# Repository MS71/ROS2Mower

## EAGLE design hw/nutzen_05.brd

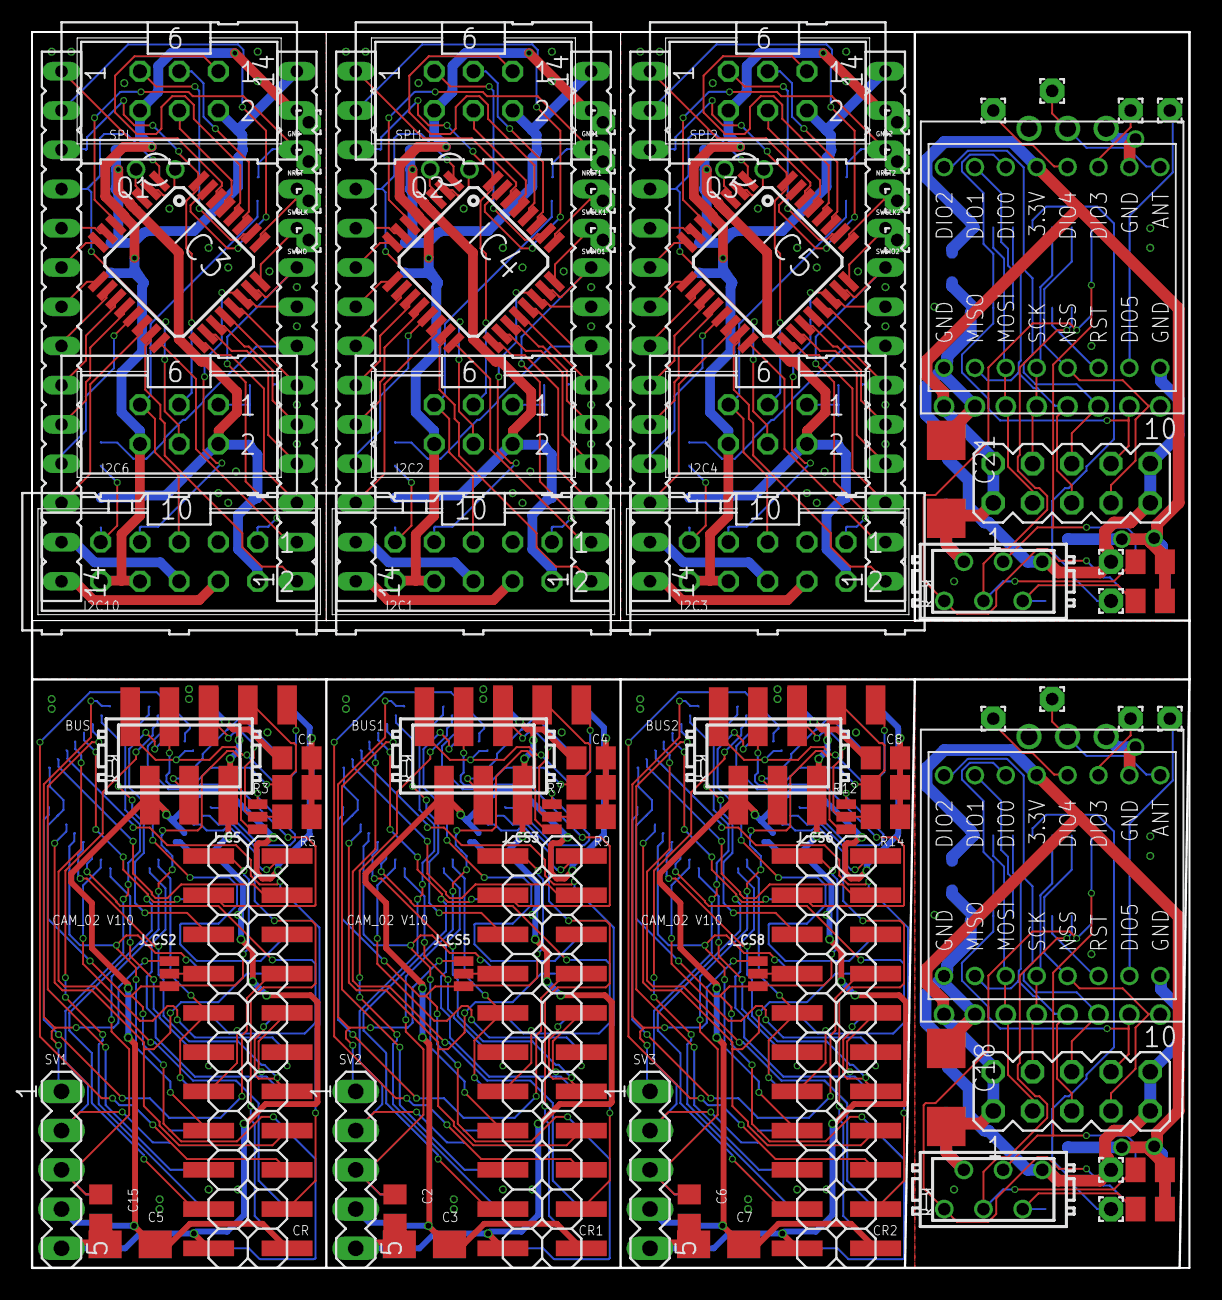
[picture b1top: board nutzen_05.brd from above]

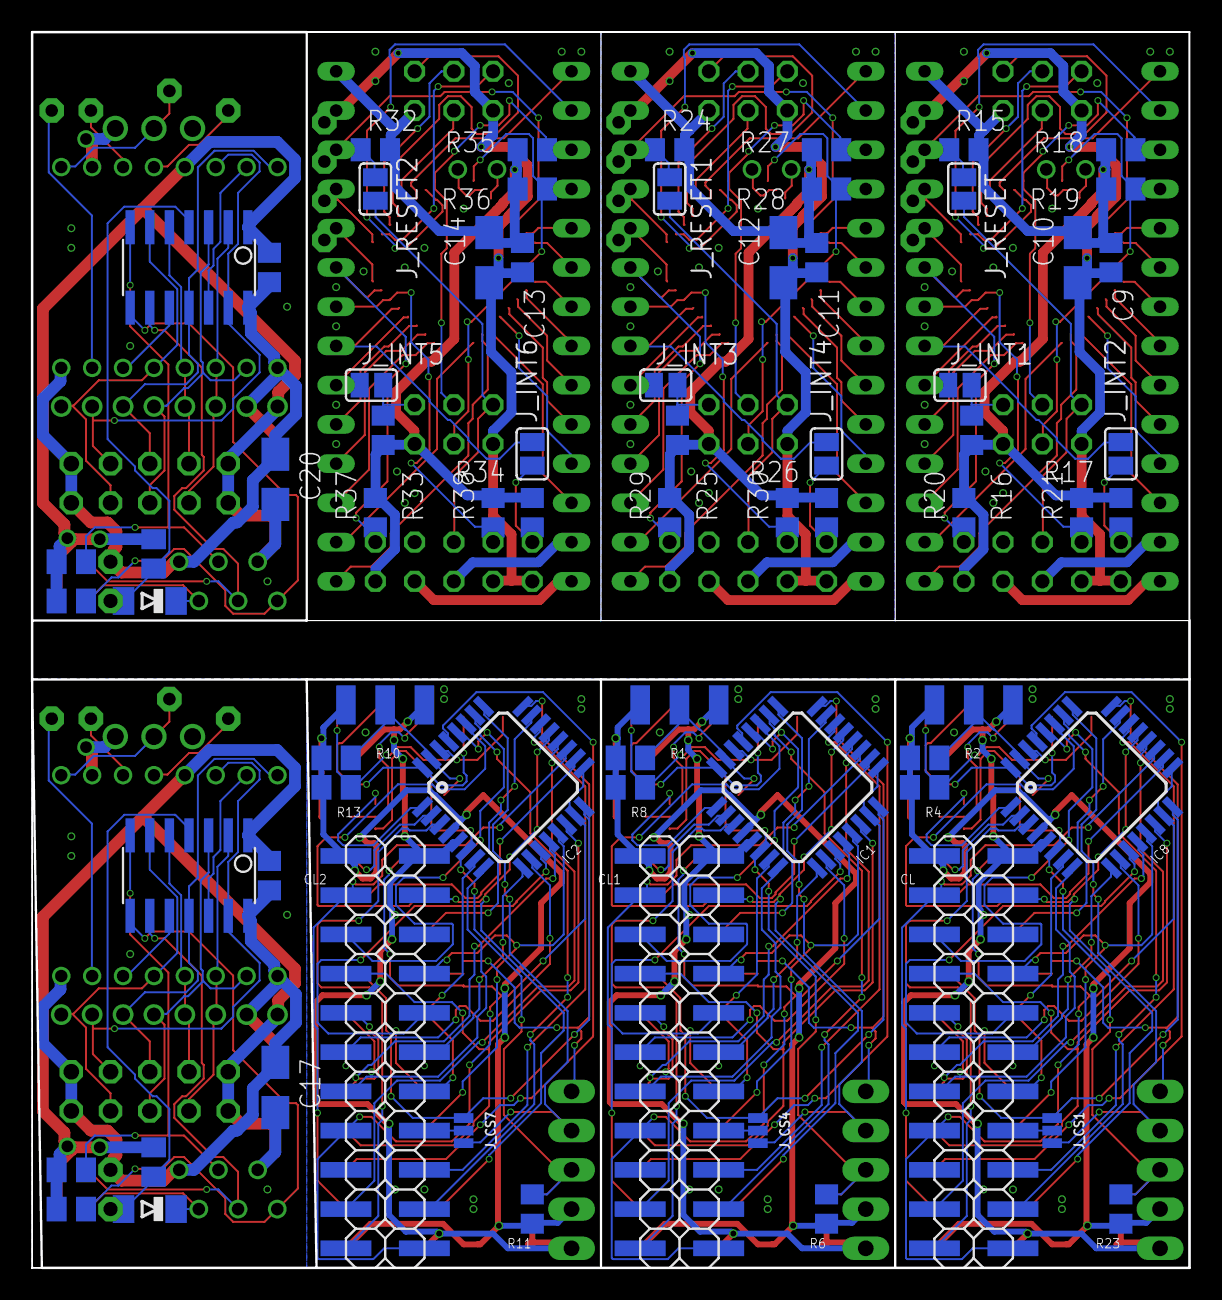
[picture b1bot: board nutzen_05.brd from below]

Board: 2 copper layers, 74.9 x 80.0 mm, 175 parts (77 on the bottom side), 251 nets.

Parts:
BUS, BUS1, BUS2: MICROMATCH-6SMD
C1, C2, C4, C6, C8, C15: 0.1; C0805
C3, C5, C7, C17, C20: 10u; B/3528-21W
C9, C11, C13: C0805
C10, C12, C14: B/3528-21W
C16, C19: 100n; C0805
C18, C21: C/6032-28R
CL, CL1, CL2: 2X11SMD
CR, CR1, CR2: 2X11SMD
D1, D2: MINIMELF
DW, DW1: 1,6/0,9
GND, GND1, GND2: 1,6/0,8
GND_, GND_1: 1,6/0,9
I2C1, I2C3, I2C10: ML10
I2C2, I2C4, I2C6: ML6
IC1, IC2, IC8: STM32G071KBT6N; LQFP-32
IC3, IC4, IC5: STM32G071; LQFP-32
IC6, IC7: TINY84 or TINY841; SOIC14
J_CS, J_CS1, J_CS2, J_CS3, J_CS4, J_CS5, J_CS6, J_CS7, J_CS8: SMT-JUMPER_3_1-NC_PASTE_NO-SILK
J_INT1, J_INT2, J_INT3, J_INT4, J_INT5, J_INT6: SJ
J_RESET, J_RESET1, J_RESET2: SJ
L, L1, L2: FE14
NRST, NRST1, NRST2: 1,6/0,8
PAD1, PAD2, PAD3, PAD4, PAD5, PAD6, PAD7, PAD8, PAD9, PAD10, PAD11, PAD12, PAD13, PAD14, PAD15, PAD16, PAD17, PAD18: SMD1,27-2,54
PAD19, PAD20, PAD21, PAD22, PAD23, PAD24, PAD25, PAD26: 1,6/0,8
Q1, Q2, Q3: TC26V
R, R22, R31: FE14
R1, R2, R3, R4, R5, R7, R8, R9, R10, R12, R13, R14, R39, R40, R41, R42, R43, R44, R45, R46, R47, R48: 10k; M0805
R6, R11, R23: 100K; R0805
R15, R16, R17, R18, R19, R20, R21, R24, R25, R26, R27, R28, R29, R30, R32, R33, R34, R35, R36, R37, R38: R0805
SPI, SPI1, SPI2: ML6
SV1, SV2, SV3: MA05-1
SV4, SV5: MA05-2
SWCLK, SWCLK1, SWCLK2: 1,6/0,8
SWDIO, SWDIO1, SWDIO2: 1,6/0,8
U$1, U$2: CC1101
U$3, U$4: WIRELESS-LORA-RFM95W#THT
X1, X2: BUS; MICROMATCH-6

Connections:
BUS_INT: IC6.8, R42.2, X1.1
BUS_INT1: IC7.8, R47.2, X2.1
BUS_P1: BUS1.5, J_CS3.2, PAD11.1, R9.2
BUS_P2: BUS2.5, J_CS6.2, PAD17.1, R14.2
BUS_P5: BUS.5, J_CS.2, PAD5.1, R5.2
BUS_RESET: I2C6.5, I2C10.5, J_RESET.1
BUS_RESET1: I2C1.5, I2C2.5, J_RESET1.1
BUS_RESET2: I2C3.5, I2C4.5, J_RESET2.1
BUS_RESET3: D2.C, R43.2, X1.5
BUS_RESET4: D1.C, R48.2, X2.5
BUS_SCL: IC6.9, R41.2, X1.3
BUS_SCL1: IC7.9, R46.2, X2.3
BUS_SDA: IC6.7, R40.2, X1.4
BUS_SDA1: IC7.7, R45.2, X2.4
CL_OE: CL.20, IC8.26
CL_OE1: CL1.20, IC1.26
CL_OE2: CL2.20, IC2.26
CL_PWDN: CL.16, J_CS1.2
CL_PWDN1: CL1.16, J_CS4.2
CL_PWDN2: CL2.16, J_CS7.2
CL_RCK: CL.18, IC8.22
CL_RCK1: CL1.18, IC1.22
CL_RCK2: CL2.18, IC2.22
CL_RST: CL.15, CL.22, CR.22, IC8.15, IC8.17, J_CS2.3
CL_RST1: CL1.15, CL1.22, CR1.22, IC1.15, IC1.17, J_CS5.3
CL_RST2: CL2.15, CL2.22, CR2.22, IC2.15, IC2.17, J_CS8.3
CL_VSYNC: CL.5, IC8.28
CL_VSYNC1: CL1.5, IC1.28
CL_VSYNC2: CL2.5, IC2.28
CL_WR: CL.19, IC8.20
CL_WR1: CL1.19, IC1.20
CL_WR2: CL2.19, IC2.20
CL_WRST: CL.21, IC8.3
CL_WRST1: CL1.21, IC1.3
CL_WRST2: CL2.21, IC2.3
CR_OE: CR.20, IC8.27
CR_OE1: CR1.20, IC1.27
CR_OE2: CR2.20, IC2.27
CR_PWDN: CR.16, J_CS2.2
CR_PWDN1: CR1.16, J_CS5.2
CR_PWDN2: CR2.16, J_CS8.2
CR_RCK: CR.18, IC8.23
CR_RCK1: CR1.18, IC1.23
CR_RCK2: CR2.18, IC2.23
CR_RST: CR.15, IC8.16, J_CS1.3
CR_RST1: CR1.15, IC1.16, J_CS4.3
CR_RST2: CR2.15, IC2.16, J_CS7.3
CR_VSYNC: CR.5, IC8.29
CR_VSYNC1: CR1.5, IC1.29
CR_VSYNC2: CR2.5, IC2.29
CR_WR: CR.19, IC8.18
CR_WR1: CR1.19, IC1.18
CR_WR2: CR2.19, IC2.18
CR_WRST: CR.21, IC8.2
CR_WRST1: CR1.21, IC1.2
CR_WRST2: CR2.21, IC2.2
CS0: IC6.6, SV4.7, U$1.CSN, U$3.A5
CS1: IC7.6, SV5.7, U$2.CSN, U$4.A5
C_D0: CL.14, CR.14, IC8.7
C_D1: CL.13, CR.13, IC8.8
C_D2: CL.12, CR.12, IC8.9
C_D3: CL.11, CR.11, IC8.10
C_D4: CL.10, CR.10, IC8.11
C_D5: CL.9, CR.9, IC8.12
C_D6: CL.8, CR.8, IC8.13
C_D7: CL.7, CR.7, IC8.14
C_D8: CL1.7, CR1.7, IC1.14
C_D9: CL1.8, CR1.8, IC1.13
C_D10: CL1.9, CR1.9, IC1.12
C_D11: CL1.10, CR1.10, IC1.11
C_D12: CL1.11, CR1.11, IC1.10
C_D13: CL1.12, CR1.12, IC1.9
C_D14: CL1.13, CR1.13, IC1.8
C_D15: CL1.14, CR1.14, IC1.7
C_D16: CL2.7, CR2.7, IC2.14
C_D17: CL2.8, CR2.8, IC2.13
C_D18: CL2.9, CR2.9, IC2.12
C_D19: CL2.10, CR2.10, IC2.11
C_D20: CL2.11, CR2.11, IC2.10
C_D21: CL2.12, CR2.12, IC2.9
C_D22: CL2.13, CR2.13, IC2.8
C_D23: CL2.14, CR2.14, IC2.7
DW: D2.A, DW.1, IC6.4, R39.2
DW1: D1.A, DW1.1, IC7.4, R44.2
GND: BUS.6, C1.2, C5.-, C15.2, CL.2, CR.2, IC8.5, PAD6.1, SV1.5
GND1: BUS1.6, C2.2, C3.-, C4.2, CL1.2, CR1.2, IC1.5, PAD12.1, SV2.5
GND2: BUS2.6, C6.2, C7.-, C8.2, CL2.2, CR2.2, IC2.5, PAD18.1, SV3.5
GND3: C9.2, C10.-, GND.1, I2C6.6, I2C10.8, I2C10.10, IC3.5, R.13, SPI.6
GND4: C11.2, C12.-, GND1.1, I2C1.8, I2C1.10, I2C2.6, IC4.5, R22.13, SPI1.6
GND5: C13.2, C14.-, GND2.1, I2C3.8, I2C3.10, I2C4.6, IC5.5, R31.13, SPI2.6
GND6: C16.2, C17.-, C18.-, GND_.1, IC6.14, SV4.9, SV4.10, U$1.GND0, U$1.GND1, U$1.GND2, U$3.A1, U$3.A8, U$3.B7, X1.6
GND7: C19.2, C20.-, C21.-, GND_1.1, IC7.14, SV5.9, SV5.10, U$2.GND0, U$2.GND1, U$2.GND2, U$4.A1, U$4.A8, U$4.B7, X2.6
GPIO0: IC6.13, SV4.8, U$1.GDO0, U$3.B3
GPIO1: IC6.12, U$3.B2
GPIO2: IC6.11, SV4.6, U$1.GDO2, U$3.B1
GPIO3: IC7.13, SV5.8, U$2.GDO0, U$4.B3
GPIO4: IC7.11, SV5.6, U$2.GDO2, U$4.B1
GPIO5: IC7.12, U$4.B2
INT1: I2C6.1, J_INT1.1, R16.1
INT2: I2C10.9, J_INT2.1, R17.1
INT3: I2C2.1, J_INT3.1, R25.1
INT4: I2C1.9, J_INT4.1, R26.1
INT5: I2C4.1, J_INT5.1, R33.1
INT6: I2C3.9, J_INT6.1, R34.1
MISO: IC6.3, SV4.5, U$1.SO, U$3.A2
MISO1: IC7.3, SV5.5, U$2.SO, U$4.A2
MOSI: IC6.2, SV4.3, U$1.SI, U$3.A3
MOSI1: IC7.2, SV5.3, U$2.SI, U$4.A3
unnamed: IC4.2, Q2.2
unnamed: IC4.3, Q2.1
unnamed: IC5.2, Q3.2
unnamed: IC5.3, Q3.1
unnamed: PAD19.1, U$1.ANT, U$3.B8
unnamed: PAD20.1, U$3.B6
unnamed: PAD21.1, U$3.B5
unnamed: PAD22.1, U$3.A7
unnamed: PAD23.1, U$2.ANT, U$4.B8
unnamed: PAD24.1, U$4.B6
unnamed: PAD25.1, U$4.B5
unnamed: PAD26.1, U$4.A7
unnamed: IC3.2, Q1.2
unnamed: IC3.3, Q1.1
NRST: IC3.6, J_RESET.2, NRST.1, R.12, R15.1
NRST1: IC4.6, J_RESET1.2, NRST1.1, R22.12, R24.1
NRST2: IC5.6, J_RESET2.2, NRST2.1, R31.12, R32.1
PA0: IC3.7, L.5
PA1: IC3.8, L.6
PA2: IC3.9, L.7
PA3: IC3.10, L.8
PA4: IC3.11, L.9
PA5: IC3.12, L.10
PA6: IC3.13, L.11
PA7: IC3.14, L.12
PA8: IC3.18, R.4
PA9: IC3.19, R.5
PA10: IC3.21, J_INT2.2, R.7
PA11: IC4.7, L1.5
PA12: IC4.8, L1.6
PA13: IC4.9, L1.7
PA14: IC4.10, L1.8
PA15: IC4.11, L1.9
PA16: IC4.12, L1.10
PA17: IC4.18, R22.4
PA18: IC4.19, R22.5
PA19: IC4.13, L1.11
PA20: IC4.14, L1.12
PA21: IC4.21, J_INT4.2, R22.7
PA22: IC5.7, L2.5
PA23: IC5.8, L2.6
PA24: IC5.9, L2.7
PA25: IC5.10, L2.8
PA26: IC5.11, L2.9
PA27: IC5.12, L2.10
PA28: IC5.18, R31.4
PA29: IC5.19, R31.5
PA30: IC5.13, L2.11
PA31: IC5.14, L2.12
PA32: IC5.21, J_INT6.2, R31.7
PB0: IC3.15, R.1
PB1: IC3.16, R.2
PB2: IC4.16, R22.2
PB3: IC4.17, R22.3
PB4: IC4.30, L1.1
PB5: IC4.15, R22.1
PB6: IC3.30, L.1
PB7: IC3.31, L.2
PB8: IC4.31, L1.2
PB9: IC5.16, R31.2
PB10: IC5.17, R31.3
PB11: IC5.30, L2.1
PB12: IC5.15, R31.1
PB13: IC5.31, L2.2
PB15: IC3.17, R.3
PC1: IC4.20, J_INT3.2, R22.6
PC2: IC5.20, J_INT5.2, R31.6
PC6: IC3.20, J_INT1.2, R.6
RESOUT: IC6.10, U$3.A6
RESOUT1: IC7.10, U$4.A6
SCK: IC6.5, SV4.4, U$1.SCLK, U$3.A4
SCK1: IC7.5, SV5.4, U$2.SCLK, U$4.A4
SCL: CL.3, CR.3, IC8.19
SCL1: CL1.3, CR1.3, IC1.19
SCL2: CL2.3, CR2.3, IC2.19
SCL3: I2C6.3, IC3.32, L.3, R18.1
SCL4: I2C10.7, IC3.22, R.8, R21.1
SCL5: I2C2.3, IC4.32, L1.3, R27.1
SCL6: I2C1.7, IC4.22, R22.8, R30.1
SCL7: I2C4.3, IC5.32, L2.3, R35.1
SCL8: I2C3.7, IC5.22, R31.8, R38.1
SDA: CL.4, CR.4, IC8.21
SDA1: CL1.4, CR1.4, IC1.21
SDA2: CL2.4, CR2.4, IC2.21
SDA3: I2C6.4, IC3.1, L.4, R19.1
SDA4: I2C10.1, IC3.23, R.9, R20.1
SDA5: I2C2.4, IC4.1, L1.4, R28.1
SDA6: I2C1.1, IC4.23, R22.9, R29.1
SDA7: I2C4.4, IC5.1, L2.4, R36.1
SDA8: I2C3.1, IC5.23, R31.9, R37.1
SPI1_MISO: IC3.28, SPI.1
SPI1_MISO1: IC4.28, SPI1.1
SPI1_MISO2: IC5.28, SPI2.1
SPI1_MOSI: IC3.29, SPI.4
SPI1_MOSI1: IC4.29, SPI1.4
SPI1_MOSI2: IC5.29, SPI2.4
SPI1_SCK: IC3.27, SPI.3
SPI1_SCK1: IC4.27, SPI1.3
SPI1_SCK2: IC5.27, SPI2.3
SPI1_SS: IC3.26, SPI.5
SPI1_SS1: IC4.26, SPI1.5
SPI1_SS2: IC5.26, SPI2.5
SPI_CS: IC8.1, J_CS.1
SPI_CS1: IC1.1, J_CS3.1
SPI_CS2: IC2.1, J_CS6.1
SPI_MISO: BUS.1, IC8.30, PAD1.1, R4.2
SPI_MISO1: BUS1.1, IC1.30, PAD7.1, R8.2
SPI_MISO2: BUS2.1, IC2.30, PAD13.1, R13.2
SPI_MOSI: BUS.4, IC8.31, PAD4.1, R2.2
SPI_MOSI1: BUS1.4, IC1.31, PAD10.1, R1.2
SPI_MOSI2: BUS2.4, IC2.31, PAD16.1, R10.2
SPI_SCK: BUS.3, IC8.32, PAD3.1, R3.2
SPI_SCK1: BUS1.3, IC1.32, PAD9.1, R7.2
SPI_SCK2: BUS2.3, IC2.32, PAD15.1, R12.2
SWCLK: IC8.25, J_CS1.1, SV1.2
SWCLK1: IC1.25, J_CS4.1, SV2.2
SWCLK2: IC2.25, J_CS7.1, SV3.2
SWCLK3: IC3.25, R.11, SWCLK.1
SWCLK4: IC4.25, R22.11, SWCLK1.1
SWCLK5: IC5.25, R31.11, SWCLK2.1
SWDIO: IC8.24, J_CS2.1, SV1.1
SWDIO1: IC1.24, J_CS5.1, SV2.1
SWDIO2: IC2.24, J_CS8.1, SV3.1
SWDIO3: IC3.24, R.10, SWDIO.1
SWDIO4: IC4.24, R22.10, SWDIO1.1
SWDIO5: IC5.24, R31.10, SWDIO2.1
SWRES: C15.1, IC8.6, J_CS.3, R23.1, SV1.3
SWRES1: C2.1, IC1.6, J_CS3.3, R6.1, SV2.3
SWRES2: C6.1, IC2.6, J_CS6.3, R11.1, SV3.3
U1: I2C1.4, L1.14
U2: I2C3.4, L2.14
U3.1: BUS1.2, C3.+, C4.1, CL1.1, CR1.1, IC1.4, PAD8.1, R1.1, R6.2, R7.1, R8.1, R9.1, SV2.4
U3.2: BUS2.2, C7.+, C8.1, CL2.1, CR2.1, IC2.4, PAD14.1, R10.1, R11.2, R12.1, R13.1, R14.1, SV3.4
U3.3: BUS.2, C1.1, C5.+, CL.1, CR.1, IC8.4, PAD2.1, R2.1, R3.1, R4.1, R5.1, R23.2, SV1.4
U5: I2C10.4, L.14
UBAT: I2C10.6, L.13
UBAT1: I2C1.6, L1.13
UBAT2: I2C3.6, L2.13
VCC: C9.1, C10.+, I2C6.2, I2C10.2, IC3.4, R.14, R15.2, R16.2, R17.2, R18.2, R19.2, R20.2, R21.2, SPI.2
VCC1: C11.1, C12.+, I2C1.2, I2C2.2, IC4.4, R22.14, R24.2, R25.2, R26.2, R27.2, R28.2, R29.2, R30.2, SPI1.2
VCC2: C13.1, C14.+, I2C3.2, I2C4.2, IC5.4, R31.14, R32.2, R33.2, R34.2, R35.2, R36.2, R37.2, R38.2, SPI2.2
VCC3: C16.1, C17.+, C18.+, IC6.1, R39.1, R40.1, R41.1, R42.1, R43.1, SV4.1, SV4.2, U$1.VCC, U$3.B4, X1.2
VCC4: C19.1, C20.+, C21.+, IC7.1, R44.1, R45.1, R46.1, R47.1, R48.1, SV5.1, SV5.2, U$2.VCC, U$4.B4, X2.2

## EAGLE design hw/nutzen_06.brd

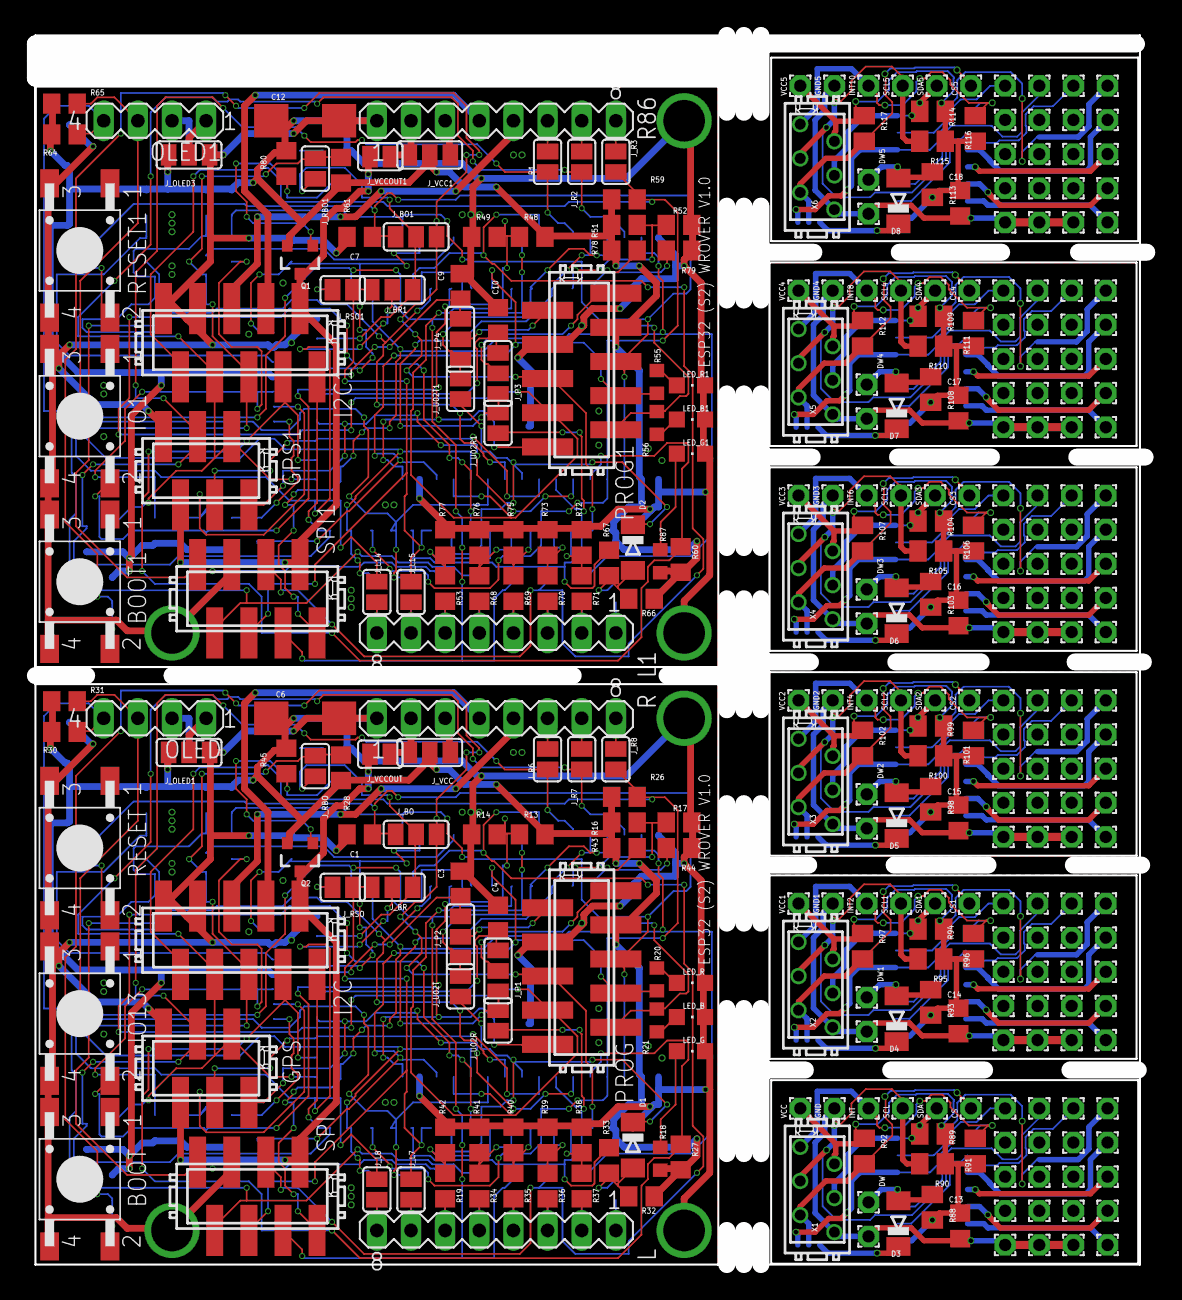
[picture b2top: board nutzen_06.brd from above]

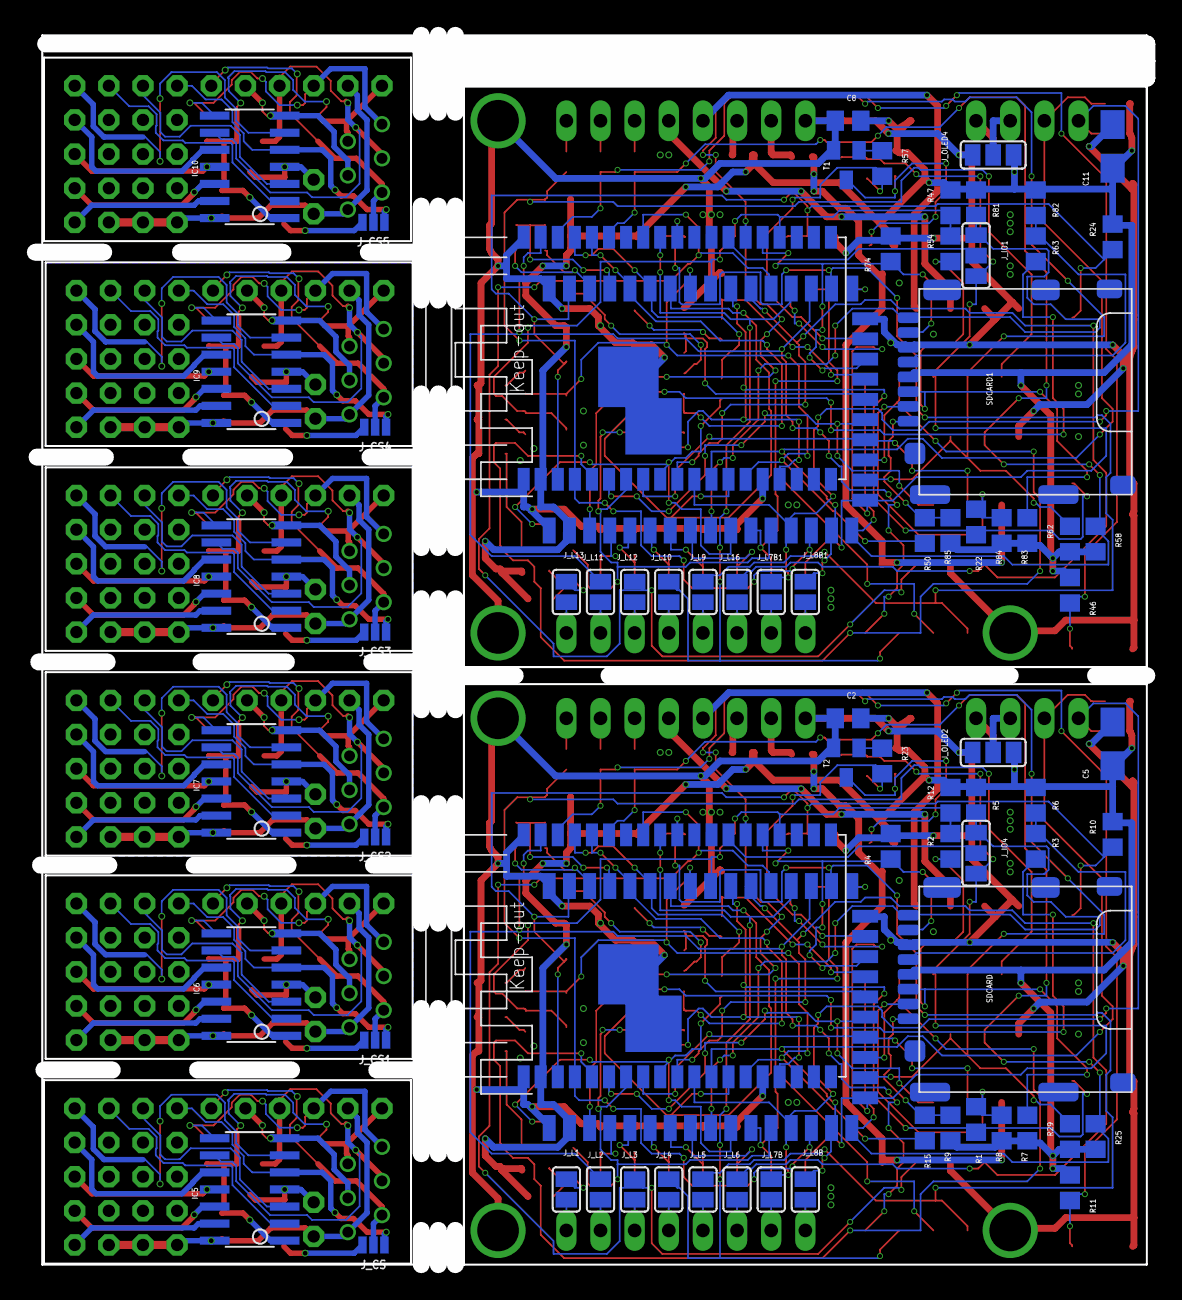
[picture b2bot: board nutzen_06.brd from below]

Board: 2 copper layers, 82.7 x 91.4 mm, 416 parts (76 on the bottom side), 238 nets.

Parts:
BOOT, BOOT1: TASTER-9314_SMD
C1, C2, C7, C8: 0.1; C0805
C3, C4, C9, C10: 22p; C0805
C5, C11: 10u; B/3528-21W
C6, C12: C/6032-28R
C13, C14, C15, C16, C17, C18: 100n; C0805
CS, CS1, CS2, CS3, CS4, CS5: 1,6/0,9
D1, D2: 4148; MINIMELF
D3, D4, D5, D6, D7, D8: MINIMELF
DW, DW1, DW2, DW3, DW4, DW5: 1,6/0,9
GND, GND1, GND2, GND3, GND4, GND5: 1,6/0,9
GND_, GND_1, GND_2, GND_3, GND_4, GND_5: 1,6/0,9
GPS, GPS1: GPS; MICROMATCH-6SMD
I2C, I2C1: I2CBUS; MICROMATCH-10SMD
IC1, IC3: ESP32-S2_WROVER; ESP32-S2-WROVER
IC2, IC4: ESP32-WROVER
IC5, IC6, IC7, IC8, IC9, IC10: TINY84 or TINY841; SOIC14
INT, INT0, INT1, INT2, INT3, INT4, INT5, INT6, INT7, INT8, INT9, INT10: 1,6/0,9
IO1, IO13: TASTER-9314_SMD
J_BO, J_BO1: SJ_2
J_BR, J_BR1: SJ_2
J_CS, J_CS1, J_CS2, J_CS3, J_CS4, J_CS5: SMT-JUMPER_3_1-NC_PASTE_NO-SILK
J_IO1, J_IO4: SJ_2
J_L1, J_L2, J_L3, J_L4, J_L5, J_L6, J_L7, J_L7B, J_L7B1, J_L8, J_L8B, J_L8B1, J_L9, J_L10, J_L11, J_L12, J_L13, J_L14, J_L15, J_L16: SJ
J_OLED1, J_OLED2, J_OLED3, J_OLED4: SJ_2
J_P1, J_P2, J_P3, J_P4: SJ_2
J_R1, J_R2, J_R3, J_R6, J_R7, J_R8: SJ
J_RBO, J_RBO1: SJ
J_RSO, J_RSO1: SJ
J_U02R, J_U02R1, J_U02T, J_U02T1: SJ
J_VCC, J_VCC1: SJ_2
J_VCCOUT, J_VCCOUT1: SJ
L, L1: MA08-1
LED_B, LED_B1: G; CHIPLED_0805
LED_G, LED_G1: G; CHIPLED_0805
LED_R, LED_R1: R; CHIPLED_0805
OLED, OLED1: MA04-1
PA0, PA1, PA2, PA3, PA4, PA5, PA6, PA7, PA8, PA9, PA10, PA11, PA12, PA13, PA14, PA15, PA16, PA17, PA18, PA19, PA20, PA21, PA22, PA23, PA24, PA25, PA26, PA27, PA28, PA29: 1,6/0,9
PAD1, PAD2, PAD3, PAD4, PAD5, PAD6, PAD7, PAD8, PAD9, PAD10, PAD11, PAD12, PAD13, PAD14, PAD15, PAD16, PAD17, PAD18, PAD19, PAD20, PAD21, PAD22, PAD23, PAD24, PAD25, PAD26, PAD27, PAD28, PAD29, PAD30, PAD31, PAD32, PAD33, PAD34, PAD35, PAD36, PAD37, PAD38, PAD39, PAD40, PAD41, PAD42, PAD43, PAD44, PAD45, PAD46, PAD47, PAD48, PAD49, PAD50, PAD51, PAD52, PAD53, PAD54, PAD55, PAD56, PAD57, PAD58, PAD59, PAD60, PAD89, PAD90, PAD91, PAD94, PAD95, PAD96, PAD97, PAD98, PAD99, PAD100, PAD101, PAD102: 1,6/0,9
PB0, PB1, PB2, PB3, PB4, PB5, PB6, PB7, PB8, PB9, PB10, PB11: 1,6/0,9
PROG, PROG1: I2CBUS; MICROMATCH-10SMD
Q1, Q2: IRLML2244; SOT23-3
R, R86: MA08-1
R1, R2, R3, R4, R5, R6, R7, R8, R9, R15, R19, R22, R25, R26, R27, R28, R29, R30, R31, R32, R33, R34, R35, R36, R37, R38, R39, R40, R41, R42, R50, R53, R54, R58, R59, R60, R61, R62, R63, R64, R65, R66, R67, R68, R69, R70, R71, R72, R73, R74, R75, R76, R77, R81, R82, R83, R84, R85: R0805
R10, R11, R12, R13, R14, R16, R17, R23, R24, R43, R44, R45, R46, R47, R48, R49, R51, R52, R57, R78, R79, R80: 10k; R0805
R18, R20, R21, R55, R56, R87: R0603
R88, R89, R90, R91, R92, R93, R94, R95, R96, R97, R98, R99, R100, R101, R102, R103, R104, R105, R106, R107, R108, R109, R110, R111, R112, R113, R114, R115, R116, R117: 10k; M0805
RESET, RESET1: TASTER-9314_SMD
SCL, SCL1, SCL2, SCL3, SCL4, SCL5: 1,6/0,9
SDA, SDA1, SDA2, SDA3, SDA4, SDA5: 1,6/0,9
SDCARD, SDCARD1: MICROSD_SD_MODE; MICRO_SD_CONNECTOR
SPI, SPI1: SPIBUS; MICROMATCH-8-SMD
T1, T2: SOT23-BEC
VCC, VCC1, VCC2, VCC3, VCC4, VCC5: 1,6/0,9
X1, X2, X3, X4, X5, X6: BUS; MICROMATCH-6

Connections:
BOOT: BOOT.2, IC1.3, IC2.IO0, J_BO.1, PROG.6, R11.1
BOOT1: BOOT1.2, IC3.3, IC4.IO0, J_BO1.1, PROG1.6, R46.1
BUS_FON: I2C.3, IC1.19, IC2.SENSOR_VN, R27.2
BUS_FON1: I2C1.3, IC3.19, IC4.SENSOR_VN, R60.2
BUS_INT: I2C.9, IC1.14, IC2.SENSOR_VP, J_R8.2, R26.2
BUS_INT1: I2C1.9, IC3.14, IC4.SENSOR_VP, J_R3.2, R59.2
BUS_INT2: IC5.8, INT.1, R91.2, X1.1
BUS_INT3: IC6.8, INT2.1, R96.2, X2.1
BUS_INT4: IC7.8, INT4.1, R101.2, X3.1
BUS_INT5: IC8.8, INT6.1, R106.2, X4.1
BUS_INT6: IC9.8, INT8.1, R111.2, X5.1
BUS_INT7: IC10.8, INT10.1, R116.2, X6.1
BUS_ON: IC1.25, J_BO.2, J_BR.1, J_RBO.2, R23.1
BUS_ON1: IC3.25, J_BO1.2, J_BR1.1, J_RBO1.2, R57.1
BUS_P1: CS1.1, J_CS1.2, R97.2, X2.5
BUS_P2: CS2.1, J_CS2.2, R102.2, X3.5
BUS_P3: CS3.1, J_CS3.2, R107.2, X4.5
BUS_P4: CS4.1, J_CS4.2, R112.2, X5.5
BUS_P5: CS.1, J_CS.2, R92.2, X1.5
BUS_P6: CS5.1, J_CS5.2, R117.2, X6.5
BUS_RESET: I2C.5, IC1.17, J_BR.2, J_IO4.3, J_L8.1, J_RBO.1, R28.2
BUS_RESET1: I2C1.5, IC3.17, J_BR1.2, J_IO1.3, J_L14.1, J_RBO1.1, R61.2
BUS_RESET2: D3.C, J_CS.3
BUS_RESET3: D4.C, J_CS1.3
BUS_RESET4: D5.C, J_CS2.3
BUS_RESET5: D6.C, J_CS3.3
BUS_RESET6: D7.C, J_CS4.3
BUS_RESET7: D8.C, J_CS5.3
BUS_SCL: GPS.2, I2C.7, IC1.18, IC2.IO22, J_R7.2, R29.2
BUS_SCL1: GPS1.2, I2C1.7, IC3.18, IC4.IO22, J_R2.2, R62.2
BUS_SCL2: IC5.9, R90.2, SCL.1, X1.3
BUS_SCL3: IC6.9, R95.2, SCL1.1, X2.3
BUS_SCL4: IC7.9, R100.2, SCL2.1, X3.3
BUS_SCL5: IC8.9, R105.2, SCL3.1, X4.3
BUS_SCL6: IC9.9, R110.2, SCL4.1, X5.3
BUS_SCL7: IC10.9, R115.2, SCL5.1, X6.3
BUS_SDA: GPS.4, I2C.1, IC1.16, IC2.IO21, J_R6.2, R25.2
BUS_SDA1: GPS1.4, I2C1.1, IC3.16, IC4.IO21, J_R1.2, R58.2
BUS_SDA2: IC5.7, R89.2, SDA.1, X1.4
BUS_SDA3: IC6.7, R94.2, SDA1.1, X2.4
BUS_SDA4: IC7.7, R99.2, SDA2.1, X3.4
BUS_SDA5: IC8.7, R104.2, SDA3.1, X4.4
BUS_SDA6: IC9.7, R109.2, SDA4.1, X5.4
BUS_SDA7: IC10.7, R114.2, SDA5.1, X6.4
DW: D3.A, DW.1, IC5.4, R88.2
DW1: D4.A, DW1.1, IC6.4, R93.2
DW2: D5.A, DW2.1, IC7.4, R98.2
DW3: D6.A, DW3.1, IC8.4, R103.2
DW4: D7.A, DW4.1, IC9.4, R108.2
DW5: D8.A, DW5.1, IC10.4, R113.2
EN: C1.1, IC1.41, IC2.EN, J_BO.3, PROG.5, R10.1, RESET.2
EN1: C7.1, IC3.41, IC4.EN, J_BO1.3, PROG1.5, R24.1, RESET1.2
GND: BOOT.3, BOOT.4, C1.2, C2.2, C3.2, C4.2, C5.-, C6.-, GPS.6, I2C.8, I2C.10, IC1.1, IC1.26, IC1.42, IC1.43, IC2.GND, IC2.GND2, IC2.GND3, IC2.GND_2, IO13.3, IO13.4, J_OLED1.1, J_OLED2.1, LED_B.C, LED_G.C, LED_R.C, PROG.4, R.1, R4.1, R14.1, R17.1, R38.2, R39.2, R40.2, R41.2, R42.2, R44.1, RESET.3, RESET.4, SDCARD.6, SPI.6, T2.E
GND1: BOOT1.3, BOOT1.4, C7.2, C8.2, C9.2, C10.2, C11.-, C12.-, GPS1.6, I2C1.8, I2C1.10, IC3.1, IC3.26, IC3.42, IC3.43, IC4.GND, IC4.GND2, IC4.GND3, IC4.GND_2, IO1.3, IO1.4, J_OLED3.1, J_OLED4.1, LED_B1.C, LED_G1.C, LED_R1.C, PROG1.4, R49.1, R52.1, R72.2, R73.2, R74.1, R75.2, R76.2, R77.2, R79.1, R86.1, RESET1.3, RESET1.4, SDCARD1.6, SPI1.6, T1.E
GND2: C13.2, GND.1, GND_.1, IC5.14, PAD100.1, PAD101.1, PAD102.1, X1.6
GND3: C14.2, GND1.1, GND_1.1, IC6.14, PAD10.1, PAD11.1, PAD12.1, X2.6
GND4: C15.2, GND2.1, GND_2.1, IC7.14, PAD22.1, PAD23.1, PAD24.1, X3.6
GND5: C16.2, GND3.1, GND_3.1, IC8.14, PAD34.1, PAD35.1, PAD36.1, X4.6
GND6: C17.2, GND4.1, GND_4.1, IC9.14, PAD46.1, PAD47.1, PAD48.1, X5.6
GND7: C18.2, GND5.1, GND_5.1, IC10.14, PAD58.1, PAD59.1, PAD60.1, X6.6
INT0: IC5.5, INT0.1, J_CS.1
INT1: IC6.5, INT1.1, J_CS1.1
INT2: IC7.5, INT3.1, J_CS2.1
INT3: IC8.5, INT5.1, J_CS3.1
INT4: IC9.5, INT7.1, J_CS4.1
INT5: IC10.5, INT9.1, J_CS5.1
LCD_1: J_OLED1.2, OLED.1
LCD_2: J_OLED2.2, OLED.2
LCD_3: J_OLED3.2, OLED1.1
LCD_4: J_OLED4.2, OLED1.2
MTCK: IC1.33, IC2.IO13, IO13.2, PROG.10, R1.2
MTCK1: IC3.33, IC4.IO13, IO1.2, PROG1.10, R22.2
MTDI: IC1.35, IC2.IO12, PROG.7, R15.2, R20.2
MTDI1: IC3.35, IC4.IO12, PROG1.7, R50.2, R55.2
MTDO: IC1.34, IC2.IO15, PROG.9, R2.2, R12.1, R21.2
MTDO1: IC3.34, IC4.IO15, PROG1.9, R47.1, R54.2, R56.2
MTMS: IC1.36, IC2.IO14, PROG.8, R3.2
MTMS1: IC3.36, IC4.IO14, PROG1.8, R63.2
unnamed: IC2.IO4, J_IO4.2
unnamed: Q2.1, R45.2, T2.C
unnamed: J_R6.1, R.6
unnamed: LED_G.A, R18.1
unnamed: J_R7.1, R.7
unnamed: J_P1.2, PROG.1
unnamed: LED_R1.A, R55.1
unnamed: LED_B1.A, R56.1
unnamed: J_L7B1.2, J_L15.2, L1.7
unnamed: J_L16.2, L1.6, R53.1
unnamed: J_L9.2, L1.5, R68.1
unnamed: J_R8.1, R.8
unnamed: J_L10.2, L1.4, R69.1
unnamed: J_L11.2, L1.2, R71.1
unnamed: J_L12.2, L1.3, R70.1
unnamed: J_L13.2, L1.1
unnamed: J_L8B1.2, J_L14.2, L1.8
unnamed: R23.2, T2.B
unnamed: J_P4.2, PROG1.2
unnamed: LED_R.A, R20.1
unnamed: LED_B.A, R21.1
unnamed: IC4.IO4, J_IO1.2
unnamed: Q1.1, R80.2, T1.C
unnamed: J_L7.2, J_L7B.2, L.7
unnamed: J_L6.2, L.6, R19.1
unnamed: R57.2, T1.B
unnamed: J_L8.2, J_L8B.2, L.8
unnamed: J_L5.2, L.5, R34.1
unnamed: J_L4.2, L.4, R35.1
unnamed: J_L2.2, L.2, R37.1
unnamed: J_L3.2, L.3, R36.1
unnamed: J_L1.2, L.1
unnamed: J_R1.1, R86.6
unnamed: J_P2.2, PROG.2
unnamed: J_R2.1, R86.7
unnamed: J_R3.1, R86.8
unnamed: LED_G1.A, R87.1
unnamed: J_P3.2, PROG1.1
OLED_SCL: IC1.15, IC2.IO27, J_L8B.1, OLED.3, R31.2
OLED_SCL1: IC3.15, IC4.IO27, J_L8B1.1, OLED1.3, R65.2
OLED_SDA: IC1.13, IC2.IO26, J_L7B.1, OLED.4, R30.2
OLED_SDA1: IC3.13, IC4.IO26, J_L7B1.1, OLED1.4, R64.2
PA0: IC5.13, PA0.1
PA1: IC5.12, PA1.1
PA2: IC5.11, PA2.1
PA3: IC5.10, PA3.1
PA4: IC6.13, PA4.1
PA5: IC6.6, PA9.1
PA6: IC6.10, PA8.1
PA7: IC5.6, PA7.1
PA8: IC6.11, PA6.1
PA9: IC6.12, PA5.1
PA10: IC7.13, PA10.1
PA11: IC7.6, PA14.1
PA12: IC7.10, PA13.1
PA13: IC7.11, PA12.1
PA14: IC7.12, PA11.1
PA15: IC8.13, PA15.1
PA16: IC8.6, PA19.1
PA17: IC8.10, PA18.1
PA18: IC8.11, PA17.1
PA19: IC8.12, PA16.1
PA20: IC9.13, PA20.1
PA21: IC9.6, PA24.1
PA22: IC9.10, PA23.1
PA23: IC9.11, PA22.1
PA24: IC9.12, PA21.1
PA25: IC10.13, PA25.1
PA26: IC10.6, PA29.1
PA27: IC10.10, PA28.1
PA28: IC10.11, PA27.1
PA29: IC10.12, PA26.1
PB0: IC5.2, PB0.1
PB1: IC5.3, PB1.1
PB2: IC6.3, PB3.1
PB3: IC6.2, PB2.1
PB4: IC7.3, PB5.1
PB5: IC7.2, PB4.1
PB6: IC8.3, PB7.1
PB7: IC8.2, PB6.1
PB8: IC9.3, PB9.1
PB9: IC9.2, PB8.1
PB10: IC10.3, PB11.1
PB11: IC10.2, PB10.1
S2_IO1: IC1.4, R37.2, R38.1
S2_IO2: IC1.5, R36.2, R39.1
S2_IO3: IC1.6, R35.2, R40.1
S2_IO4: IC1.7, R34.2, R41.1
S2_IO5: IC1.8, R19.2, R42.1
S2_IO6: IC3.8, R53.2, R77.1
S2_IO7: IC3.7, R68.2, R76.1
S2_IO8: IC3.6, R69.2, R75.1
S2_IO9: IC3.5, R70.2, R73.1
S2_IO10: IC3.4, R71.2, R72.1
S2_IO11: IC3.39, R51.1, R52.2
S2_IO12: IC3.40, R78.1, R79.2
S2_IO45: IC1.39, R16.1, R17.2
S2_IO46: IC1.40, R43.1, R44.2
SD_CLK: R3.1, R6.2, SDCARD.5
SD_CLK1: R63.1, R82.2, SDCARD1.5
SD_CMD: R2.1, R7.2, SDCARD.3
SD_CMD1: R54.1, R83.2, SDCARD1.3
SD_D0: IC1.24, IC2.IO2, R4.2, SDCARD.7
SD_D1: IC1.9, J_IO4.1, R5.2, SDCARD.8
SD_D2: R9.2, R15.1, SDCARD.1
SD_D3: R1.1, R8.2, SDCARD.2
SD_D4: IC3.9, J_IO1.1, R81.2, SDCARD1.8
SD_D5: IC3.24, IC4.IO2, R74.2, SDCARD1.7
SD_D6: R22.1, R84.2, SDCARD1.2
SD_D7: R50.1, R85.2, SDCARD1.1
SPI_CS0: IC1.28, IC2.IO5, J_L5.1, R13.1, R14.2, SPI.7
SPI_CS1: IC1.32, IC2.IO25, J_L6.1, SPI.8
SPI_CS2: IC3.32, IC4.IO25, J_L16.1, SPI1.8
SPI_CS3: IC3.28, IC4.IO5, J_L9.1, R48.1, R49.2, SPI1.7
SPI_MISO: IC1.29, IC2.IO23, J_L2.1, SPI.1
SPI_MISO1: IC3.29, IC4.IO23, J_L11.1, SPI1.1
SPI_MOSI: IC1.31, IC2.IO19, J_L3.1, SPI.4
SPI_MOSI1: IC3.31, IC4.IO19, J_L12.1, SPI1.4
SPI_ON: IC1.27, J_RSO.2
SPI_ON1: IC3.27, J_RSO1.2
SPI_RESET: IC1.11, J_BR.3, J_L7.1, J_RSO.1, SPI.5
SPI_RESET1: IC3.11, J_BR1.3, J_L15.1, J_RSO1.1, SPI1.5
SPI_SCK: IC1.30, IC2.IO18, J_L4.1, SPI.3
SPI_SCK1: IC3.30, IC4.IO18, J_L10.1, SPI1.3
U0RXD: IC1.38, IC2.RXD0, J_P1.3, J_U02R.1
U0RXD1: IC3.38, IC4.RXD0, J_P3.3, J_U02R1.1
U0TXD: IC1.37, IC2.TXD0, J_P2.3, J_U02T.1
U0TXD1: IC3.37, IC4.TXD0, J_P4.3, J_U02T1.1
U1: I2C1.4, R86.4
U1RXD: GPS.1, IC1.21, IC2.IO34
U1RXD1: GPS1.1, IC3.21, IC4.IO34
U1TXD: GPS.3, IC1.20, IC2.IO32
U1TXD1: GPS1.3, IC3.20, IC4.IO32
U2RXD: IC1.12, IC2.IO35, J_U02R.2, R33.2
U2RXD1: IC3.12, IC4.IO35, J_U02R1.2, R67.2
U2TXD: D1.C, IC1.10, IC2.IO33, J_U02T.2
U2TXD1: D2.C, IC3.10, IC4.IO33, J_U02T1.2
U2_BUS: D1.A, J_L1.1, R32.1, R33.1
U2_BUS1: D2.A, J_L13.1, R66.1, R67.1
U5: I2C.4, R.4
U33A: J_VCC.3, J_VCCOUT.2, R.2
U33A1: J_VCC1.3, J_VCCOUT1.2, R86.2
U33B: J_VCC.1, R.3
U33B1: J_VCC1.1, R86.3
UBAT: I2C.6, R.5
UBAT1: I2C1.6, R86.5
UBUS: GPS.5, I2C.2, J_VCCOUT.1, Q2.3, SPI.2
UBUS1: GPS1.5, I2C1.2, J_VCCOUT1.1, Q1.3, SPI1.2
USBN: C4.1, IC1.22, J_P1.1
USBN1: C10.1, IC3.22, J_P3.1
USBP: C3.1, IC1.23, J_P2.1
USBP1: C9.1, IC3.23, J_P4.1
VCC: C2.1, C5.+, C6.+, IC1.2, IC2.VDD33, J_OLED1.3, J_OLED2.3, J_VCC.2, PROG.3, Q2.2, R5.1, R6.1, R7.1, R8.1, R9.1, R10.2, R11.2, R12.2, R13.2, R16.2, R18.2, R25.1, R26.1, R27.1, R28.1, R29.1, R30.1, R31.1, R32.2, R43.2, R45.1, SDCARD.4
VCC1: C8.1, C11.+, C12.+, IC3.2, IC4.VDD33, J_OLED3.3, J_OLED4.3, J_VCC1.2, PROG1.3, Q1.2, R24.2, R46.2, R47.2, R48.2, R51.2, R58.1, R59.1, R60.1, R61.1, R62.1, R64.1, R65.1, R66.2, R78.2, R80.1, R81.1, R82.1, R83.1, R84.1, R85.1, R87.2, SDCARD1.4
VCC2: C13.1, IC5.1, R88.1, R89.1, R90.1, R91.1, R92.1, VCC.1, X1.2
VCC3: C14.1, IC6.1, R93.1, R94.1, R95.1, R96.1, R97.1, VCC1.1, X2.2
VCC4: C15.1, IC7.1, R98.1, R99.1, R100.1, R101.1, R102.1, VCC2.1, X3.2
VCC5: C16.1, IC8.1, R103.1, R104.1, R105.1, R106.1, R107.1, VCC3.1, X4.2
VCC6: C17.1, IC9.1, R108.1, R109.1, R110.1, R111.1, R112.1, VCC4.1, X5.2
VCC7: C18.1, IC10.1, R113.1, R114.1, R115.1, R116.1, R117.1, VCC5.1, X6.2

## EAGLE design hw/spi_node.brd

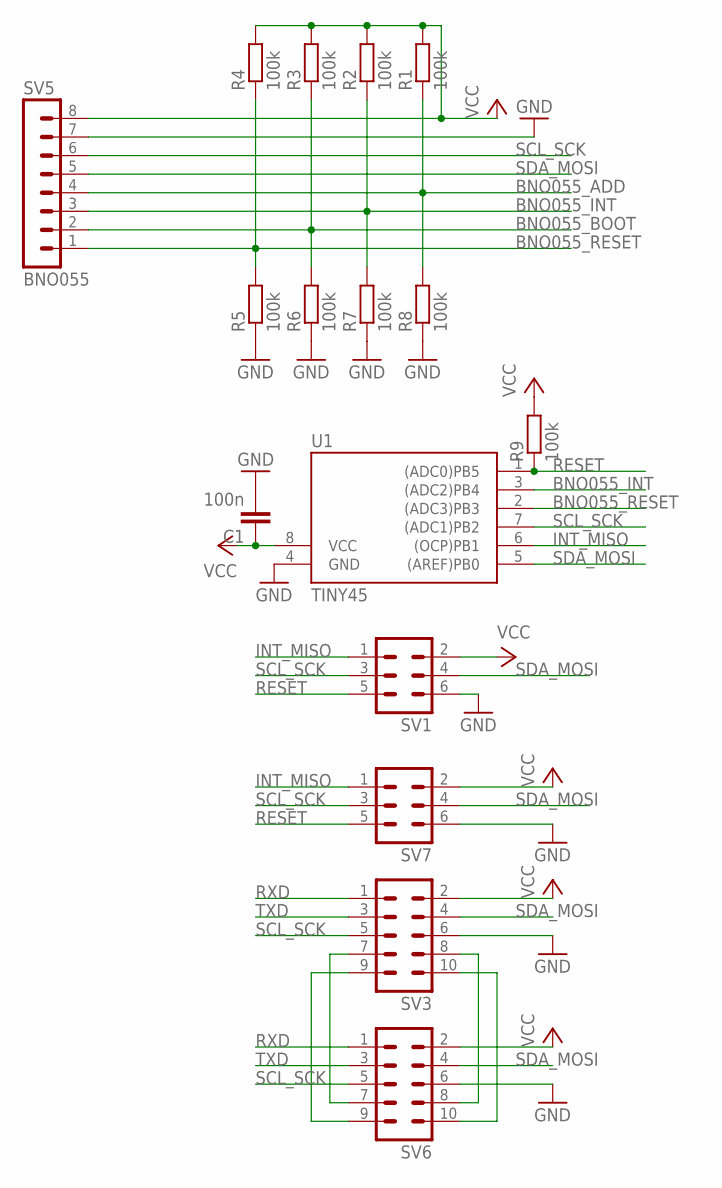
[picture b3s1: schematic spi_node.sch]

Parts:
C1: 100n; C0805
R1, R2, R3, R4, R5, R6, R7, R8, R9: 100k; M0805
SV1, SV7: ML6
SV3, SV6: ML10
SV5: BNO055; MA08-1
U1: TINY45; SOIC8

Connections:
BNO055_ADD: R1.1, R8.2, SV5.4
BNO055_BOOT: R3.1, R6.2, SV5.2
BNO055_INT: R2.1, R7.2, SV5.3, U1.3 ((ADC2)PB4)
BNO055_RESET: R4.1, R5.2, SV5.1, U1.2 ((ADC3)PB3)
GND: C1.2, R5.1, R6.1, R7.1, R8.1, SV1.6, SV3.6, SV5.7, SV6.6, SV7.6, U1.4 (GND)
INT_MISO: SV1.1, SV7.1, U1.6 ((OCP)PB1)
unnamed: SV3.7, SV6.7
unnamed: SV3.9, SV6.9
unnamed: SV3.8, SV6.8
unnamed: SV3.10, SV6.10
RESET: R9.1, SV1.5, SV7.5, U1.1 ((ADC0)PB5)
RXD: SV3.1, SV6.1
SCL_SCK: SV1.3, SV3.5, SV5.6, SV6.5, SV7.3, U1.7 ((ADC1)PB2)
SDA_MOSI: SV1.4, SV3.4, SV5.5, SV6.4, SV7.4, U1.5 ((AREF)PB0)
TXD: SV3.3, SV6.3
VCC: C1.1, R1.2, R2.2, R3.2, R4.2, R9.2, SV1.2, SV3.2, SV5.8, SV6.2, SV7.2, U1.8 (VCC)

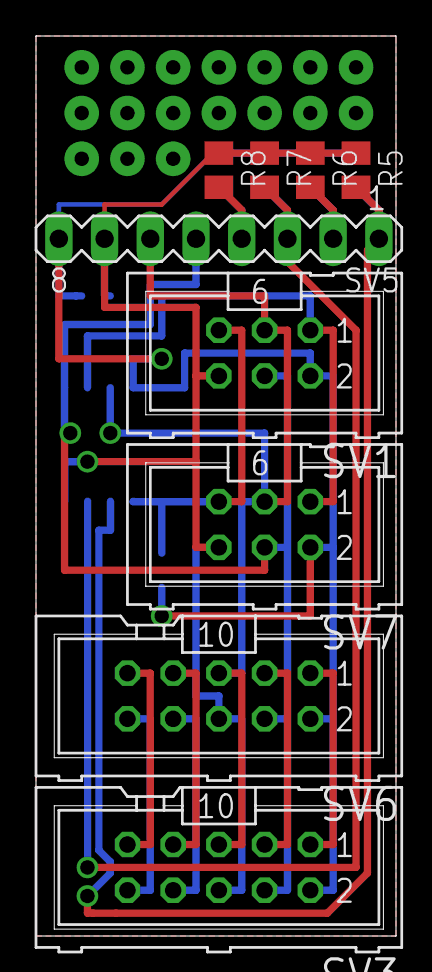
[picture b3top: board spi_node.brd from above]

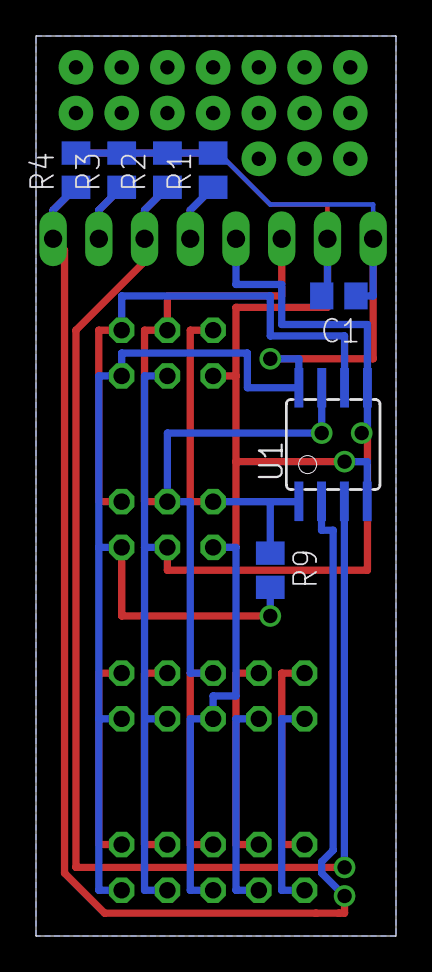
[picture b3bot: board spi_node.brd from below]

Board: 2 copper layers, 20.0 x 50.0 mm, 16 parts (7 on the bottom side), 16 nets.

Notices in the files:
parts and their libraries:
SparkFun-Jumpers: Licensing: Creative Commons ShareAlike 4.0 International - https://creativecommons.org/licenses/by-sa/4.0
modules: Released under the Creative Commons Attribution 4.0 International License: http://creativecommons.org/licenses/by/4.0
